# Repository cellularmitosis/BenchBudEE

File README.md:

BenchBudEE
==========

This is my fork of the BenchBudEE project, which is part of the Session 1 Project For Contextual Electronics.

See http://contextualelectronics.com/

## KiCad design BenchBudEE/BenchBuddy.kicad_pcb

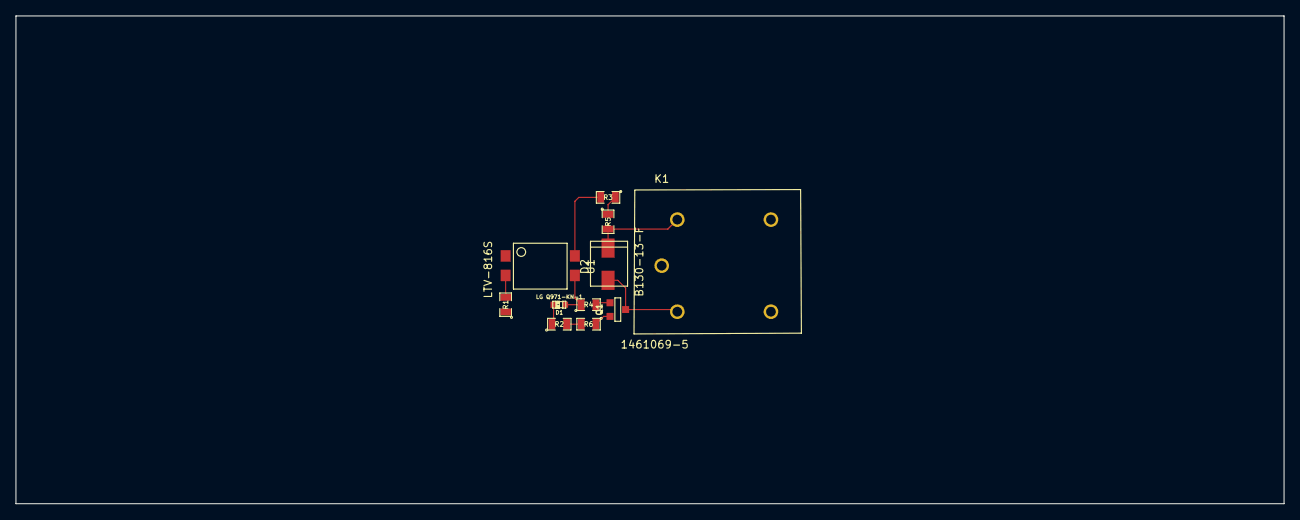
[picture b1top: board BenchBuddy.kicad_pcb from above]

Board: 4 copper layers, 165.1 x 63.5 mm, 11 parts (0 on the bottom side), 10 nets.

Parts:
D1: LG Q971-KN-1; LED-0603
D2: B130-13-F; SMA
K1: 1461069-5; TE-SPDT
Q1: 2N3904; SOT23EBC
R1: 500; SM0805
R2: 200; SM0805
R3, R5, R6: 0; SM0805
R4: 100; SM0805
U1: LTV-816S; 4-SMD

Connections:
+12P: R3.1, R5.1
GND: R2.2, R6.2
unnamed: D2.2, K1.2, R5.2
unnamed: Q1.2, R4.2
unnamed: R1.2, U1.2
unnamed: R3.2, U1.4
unnamed: D2.1, K1.5, Q1.3
unnamed: Q1.1, R6.1
unnamed: D1.2, R2.1
unnamed: D1.1, R4.1, U1.3

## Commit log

2014-02-08 Adding empty project, schematic, and layout.
2014-02-09 Pulling in PNG of block diagram.
2014-02-09 Adding hierarchical sheets to schematic
2014-02-09 Creating hierachical sheet connections.
2014-02-09 Implementing Thermocouple schematic
2014-02-10 Implementing Current / Fan Driver schematic
2014-02-10 Implementing Relay schematic.
2014-02-12 working on power / filtering schematic
2014-02-12 swapping Power and PowerAdjustmentMonitor schematics
2014-02-12 Implementing the Power schematic.
2014-02-13 Implementing current control and monitor schematic.
2014-02-13 further work on the monitoring schematic.
2014-02-24 Completing schematics from week 3 videos.
2014-02-27 hotkeys and setup
2014-03-03 syncing to https://github.com/ContextualElectronics/BenchBudEE/tree/ebd662c68b928f78643cdf924dc35a4d91f03121
2014-03-03 checking in all my local changes before syncing to chris's repo.
2014-03-03 playing with the layout
2014-03-03 syncing to upstream
2014-03-03 playing around with the routing.
2014-03-05 clearing repo
2014-03-05 syncing to upstream repo
